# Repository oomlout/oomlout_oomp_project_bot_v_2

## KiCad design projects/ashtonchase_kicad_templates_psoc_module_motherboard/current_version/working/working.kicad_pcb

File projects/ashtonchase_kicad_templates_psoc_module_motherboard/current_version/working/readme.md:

# kicad_templates
 
## summary 
* id: ashtonchase_kicad_templates_psoc_module_motherboard
* user: ashtonchase
* name: kicad_templates
* board: psoc_module_motherboard
* repo: https://github.com/ashtonchase/kicad_templates
* src_file_repo_kicad_pcb: PSoC_Module/PSoC_Module_MotherBoard.kicad_pcb
* src_file_repo_kicad_pcb_link: https://github.com/ashtonchase/kicad_templates/tree/master/PSoC_Module/PSoC_Module_MotherBoard.kicad_pcb

* src_file_repo_sch: NEMA23_Stepper/Nema23_stepper.sch
* src_file_repo_sch_link: https://github.com/ashtonchase/kicad_templates/tree/master/NEMA23_Stepper/Nema23_stepper.sch
* full details link: https://github.com/oomlout/oomlout_oomp_project_bot_v_2/tree/main/projects/ashtonchase_kicad_templates_psoc_module_motherboard/current_version/working  

## pcb  

[board (pdf)](working.pdf)  

## working_bom
| Id | Designator | Footprint | Quantity | Designation | Supplier and ref |  | None | 
| --- | --- | --- | --- | --- | --- | --- | --- | 
| 1 | C1,C3,C7,C9,C15,C16,C17,C18,C5 | R_0603_HandSoldering | 9 | 1.0UF |  |  | [''] | 
| 2 | C2,C4,C8,C10,C11,C12,C13,C14,C23,C24,C25,C28,C6 | R_0603_HandSoldering | 13 | 0.1UF |  |  | [''] | 
| 3 | C21,C22 | R_0603_HandSoldering | 2 | 22PF |  |  | [''] | 
| 4 | C26,C27 | R_1210_HandSoldering | 2 | 22UF |  |  | [''] | 
| 5 | D1,D2,D5,D6 | MiniMELF_Handsoldering | 4 | TVS |  |  | [''] | 
| 6 | D3,D4 | MiniMELF_Handsoldering | 2 | D_Schottky |  |  | [''] | 
| 7 | D7 | SOT-23 | 1 | ZHCS |  |  | [''] | 
| 8 | D8 | MiniMELF_Handsoldering | 1 | D |  |  | [''] | 
| 9 | F1 | Fuse_SMD1206_HandSoldering | 1 | FUSE |  |  | [''] | 
| 10 | JP1,JP3,JP5,JP2,JP4 | R_0805_HandSoldering | 5 | Jumper_NC_Small |  |  | [''] | 
| 11 | L1 | NR4018 | 1 | 22UH |  |  | [''] | 
| 12 | P2 | USB_Mini-B | 1 | USB_OTG |  |  | [''] | 
| 13 | P3 | BARREL_JACK | 1 | CONN_01X02 |  |  | [''] | 
| 14 | R1 | R_0603_HandSoldering | 1 | 0 |  |  | [''] | 
| 15 | R6,R7 | R_0603_HandSoldering | 2 | 22 |  |  | [''] | 
| 16 | R8,R9,R10,R11,R12,R13 | R_0603_HandSoldering | 6 | 10 |  |  | [''] | 
| 17 | R14 | R_0603_HandSoldering | 1 | 4.7K |  |  | [''] | 
| 18 | R15,R16,R17,R19,R20 | R_0805_HandSoldering | 5 | NL |  |  | [''] | 
| 19 | R18 | R_0805_HandSoldering | 1 | 0 |  |  | [''] | 
| 20 | SW1 | SW_PUSH_SMALL | 1 | SW_PUSH |  |  | [''] | 
| 21 | U1 | LQFP-100_14x14mm_Pitch0.5mm | 1 | CY8C5888AXI-LP096 |  |  | [''] | 
| 22 | Y2 | Crystal_HC49-SD_SMD | 1 | 32.768KHZ |  |  | [''] | 
| 23 | P1 | Molex_Microfit3_Header_02x05_Straight_43045-1028 | 1 | CONN_02X05 |  |  | [''] |

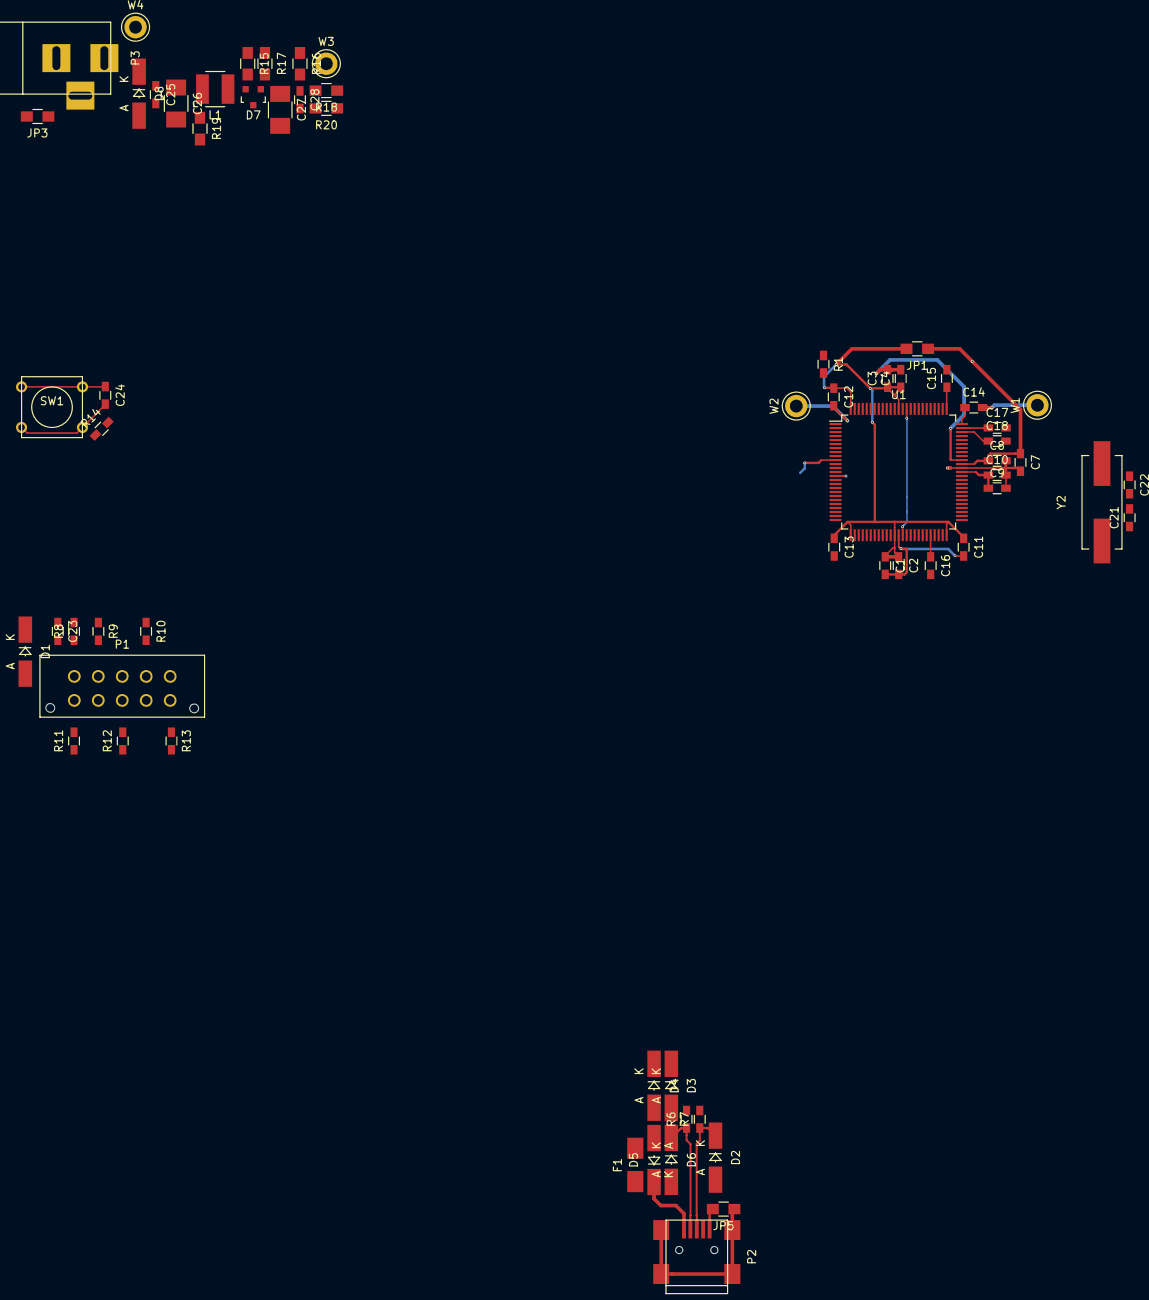
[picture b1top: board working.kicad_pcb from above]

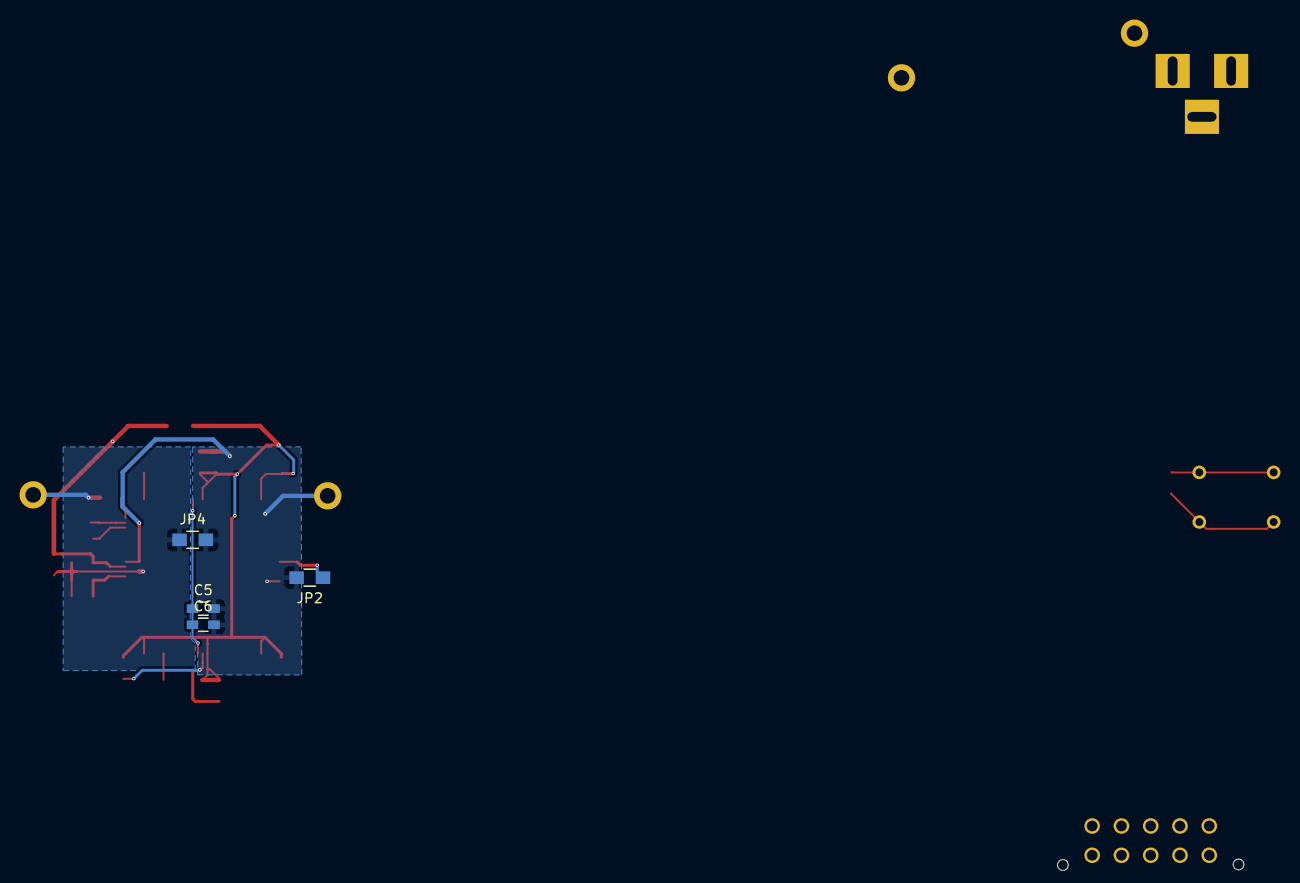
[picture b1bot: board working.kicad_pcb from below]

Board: 2 copper layers, 67 parts (4 on the bottom side), 39 nets.

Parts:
C1, C3, C5, C7, C9, C15, C16, C17, C18: 1.0UF; R_0603_HandSoldering
C2, C4, C6, C8, C10, C11, C12, C13, C14, C23, C24, C25, C28: 0.1UF; R_0603_HandSoldering
C21, C22: 22PF; R_0603_HandSoldering
C26, C27: 22UF; R_1210_HandSoldering
D1, D2, D5, D6: TVS; MiniMELF_Handsoldering
D3, D4: D_Schottky; MiniMELF_Handsoldering
D7: ZHCS; SOT-23
D8: D; MiniMELF_Handsoldering
F1: FUSE; Fuse_SMD1206_HandSoldering
JP1, JP2, JP3, JP4, JP5: Jumper_NC_Small; R_0805_HandSoldering
L1: 22UH; NR4018
P1: CONN_02X05; Molex_Microfit3_Header_02x05_Straight_43045-1028
P2: USB_OTG; USB_Mini-B
P3: CONN_01X02; BARREL_JACK
R1: 0; R_0603_HandSoldering
R6, R7: 22; R_0603_HandSoldering
R8, R9, R10, R11, R12, R13: 10; R_0603_HandSoldering
R14: 4.7K; R_0603_HandSoldering
R15, R16, R17, R19, R20: NL; R_0805_HandSoldering
R18: 0; R_0805_HandSoldering
SW1: SW_PUSH; SW_PUSH_SMALL
U1: CY8C5888AXI-LP096; LQFP-100_14x14mm_Pitch0.5mm
W1, W2, W3, W4: TEST_1P; Test_Point_Keystone_5010-5014_Multipurpose
Y2: 32.768KHZ; Crystal_HC49-SD_SMD

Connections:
/MCU/P0.2: C18.1, U1.73
/MCU/P0.3: C17.1, U1.74
/MCU/P0.4: C15.1, U1.76
/MCU/P3.2: C16.1, U1.46
/MCU/RTC_N: C22.1, U1.56, Y2.2
/MCU/RTC_P: C21.1, U1.55, Y2.1
/MCU/USBP_N: R6.2, U1.36
/MCU/USBP_P: R7.2, U1.35
/MCU/VCCA: C9.1, C10.1, U1.63
/MCU/VCCD: C5.1, C6.1, U1.39, U1.86
/PSoC Extra Circuits/USB_VCC: D5.1, F1.1, P2.1
Earth: JP5.1, P2.6
GNDA: C7.2, C8.2, C9.2, C10.2, C14.2, C15.2, C16.2, C17.2, C18.2, C21.2, C22.2, JP4.1, U1.64, W1.1
GNDD: C1.2, C2.2, C3.2, C4.2, C5.2, C6.2, C11.2, C12.2, C13.2, C23.2, C24.2, D1.2, D2.2, D5.2, D6.2, JP2.2, JP3.2, JP4.2, JP5.2, P1.3, P1.5, P1.7, P1.9, P2.5, SW1.2, U1.14, U1.38, U1.66, U1.87, W2.1
GNDPWR: JP2.1, U1.10
IND: R15.1, U1.11
unnamed: C27.1, C28.1, D7.1, R16.2, R17.2, R18.2
unnamed: D3.2, D4.2, F1.2
unnamed: D7.2, L1.2, R15.2
unnamed: P1.1, R8.1
unnamed: P1.2, R9.2
unnamed: P1.4, R10.2
unnamed: P1.6, R11.2
unnamed: P1.8, R12.2
unnamed: P1.10, R13.2
P1.0_TMS: R9.1, U1.20
P1.1_TCK: R10.1, U1.21
P1.4_TDO: R11.1, U1.24
P1.5_TDI: R12.1, U1.25
P1.6_nRST: R13.1, U1.27
USB_N: D6.1, P2.2, R6.1
USB_P: D2.1, P2.3, R7.1
VBATT: C25.1, C26.1, D8.1, L1.1, P3.1, R19.1, U1.13, W4.1
VBATT_GND: C25.2, C26.2, C27.2, C28.2, D8.2, JP3.1, P3.2, R19.2, R20.2
VBOOST: R18.1, R20.1, U1.12, W3.1
VDDA: C7.1, C8.1, C14.1, D4.1, JP1.1, R17.1, U1.65, U1.75
VDDD: C1.1, C2.1, C3.1, C4.1, C11.1, C12.1, C13.1, D3.1, JP1.2, R1.1, R16.1, U1.26, U1.37, U1.50, U1.88, U1.100
VTARG: C23.1, D1.1, R1.2, R8.2, R14.1
XRES: C24.1, R14.2, SW1.1, U1.15
